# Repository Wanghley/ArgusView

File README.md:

# ArgusView

ArgusView is an accessibility device designed to assist visually impaired individuals by providing concise audio descriptions of their surroundings.

## Project Structure

The project is organized into three main components:

### `/embedded`
Contains the ESP32-CAM based firmware that captures images and sends them to the backend for processing.

* The code is written in C using the ESP-IDF framework.
* Key components include camera interfacing, connectivity, and button handling
* The implementation for the high-level functions is found in `src/esp32`

### `/backend`
Houses the TypeScript/Express server responsible for:
- Receiving images from the ESP32-CAM
- Processing images for description generation
- Converting text descriptions to audio
- Sending audio back to the device

### `/frontend`
A quick web interface for intercepting the requests from the ESP32-CAM and displaying the results.

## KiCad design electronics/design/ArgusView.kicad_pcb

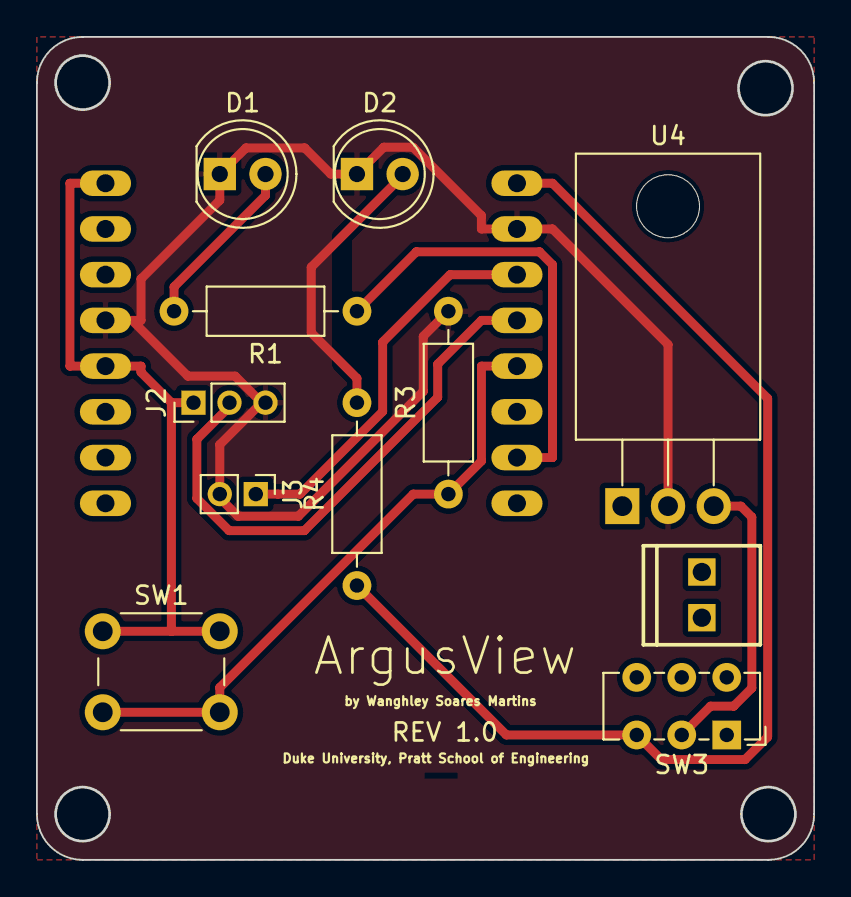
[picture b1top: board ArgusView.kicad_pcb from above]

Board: 2 copper layers, 43.2 x 45.7 mm, 12 parts (1 on the bottom side), 10 nets.

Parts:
D1: LED_SIGNAL; LED_D5.0mm
D2: LED_ON; LED_D5.0mm
J1: ConnBatt; 1X02_2.54_SCREWTERM
J2: ConnMic; PinHeader_1x03_P2.00mm_Vertical
J3: ConnSpeak; PinHeader_1x02_P2.00mm_Vertical
R1: 220R; R_Axial_DIN0207_L6.3mm_D2.5mm_P10.16mm_Horizontal
R3: 10KR; R_Axial_DIN0207_L6.3mm_D2.5mm_P10.16mm_Horizontal
R4: 330R; R_Axial_DIN0207_L6.3mm_D2.5mm_P10.16mm_Horizontal
SW1: SW_Push; SW_PUSH_6mm
SW3: SW_ON; SW_E-Switch_EG1271_SPDT
U1: ESP32-CAM
U4: LM7805_TO220; TO-220-3_Horizontal_TabDown

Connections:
GND: D1.1 (K), D2.1 (K), J2.3, J3.2, R3.2, U1.P$2 (GND), U1.P$13 (GND.), U4.2 (GND)
unnamed: D1.2 (A), R1.2
unnamed: D2.2 (A), R4.2
unnamed: J2.2, U1.P$4 (IO13)
unnamed: J3.1, U1.P$3 (IO12)
unnamed: SW3.2 (B), U4.3 (VO)
unnamed: R1.1, U1.P$7 (IO2)
unnamed: R3.1, SW1.2, U1.P$5 (IO15)
VCC: R4.1, SW3.3 (C), U1.P$1 (5V)
VDD: J2.1, SW1.1, U1.P$12 (3V3.), U1.P$16 (3V3)

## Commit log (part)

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2025-05-06 Add ArgusView KiCAD Schematics initial work
2025-05-06 Add ESP32-CAM KiCAD library as a binary file
2025-05-06 Base code for embedded and backend
2025-05-06 Can read 1KB of data
2025-05-06 Add updated ESP32-CAM library as a binary file
2025-05-06 Add image description and audio generation features with OpenAI integration
2025-05-06 Add esp32-camera component
2025-05-06 chore: update .gitignore to include electronics folder and backup files
2025-05-06 chore: update .gitignore to ignore folders in electronics/libs/
2025-05-06 checkpoint
2025-05-06 Serial monitoring working
2025-05-06 Improve image description prompt
2025-05-06 Camera is working!
2025-05-06 feat: circuit finished for protoboarding
2025-05-06 Remove components directory from Git tracking
2025-05-06 Add base code for camera and HTTP
2025-05-06 Add copilot instructions and workspace config
2025-05-06 Add drill files and job configuration for ArgusView project
    - Created ArgusView-NPTH.drl for non-plated through holes with specified coordinates and tool settings.
    - Created ArgusView-PTH.drl for plated through holes, including multiple tool sizes and detailed drilling paths.
    - Added ArgusView-job.gbrjob configuration file detailing project specifications, design rules, and file attributes for the ArgusView PCB design.
2025-05-06 Add READMEs
2025-05-06 Button behavior is irregular
2025-05-06 frontend dashboard
2025-05-06 reading audio to PSRAM. Playback via PWM working
2025-05-06 Update KiCad project files with new dimensions and wire adjustments
2025-05-06 Increase app partition size
2025-05-06 Update active layer in ArgusView.kicad_prl from 0 to 40
2025-05-06 Wifi pause working
2025-05-06 Code for microphone
2025-05-06 Add ArgusView Box v28 3D model file
2025-05-06 Final version. bug fixes
2025-05-06 Good enough audio transcription
2025-05-06 Some more code
2026-05-23 fix: remove malicious infection.
